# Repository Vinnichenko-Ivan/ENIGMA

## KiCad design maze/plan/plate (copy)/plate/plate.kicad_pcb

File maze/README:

//.........................................................................................//
// Этот код написан для соревнований RoboCup 2020 Командой Enigma                          //
// Состав команды: Винниченко Иван, Губин Сергей.                                          //
//.........................................................................................//
// This code is written for the RoboCup 2020 competition by the Enigma Team                // 
// Team: Ivan Vinnichenko, Sergey Gubin.                                                   //
//.........................................................................................//

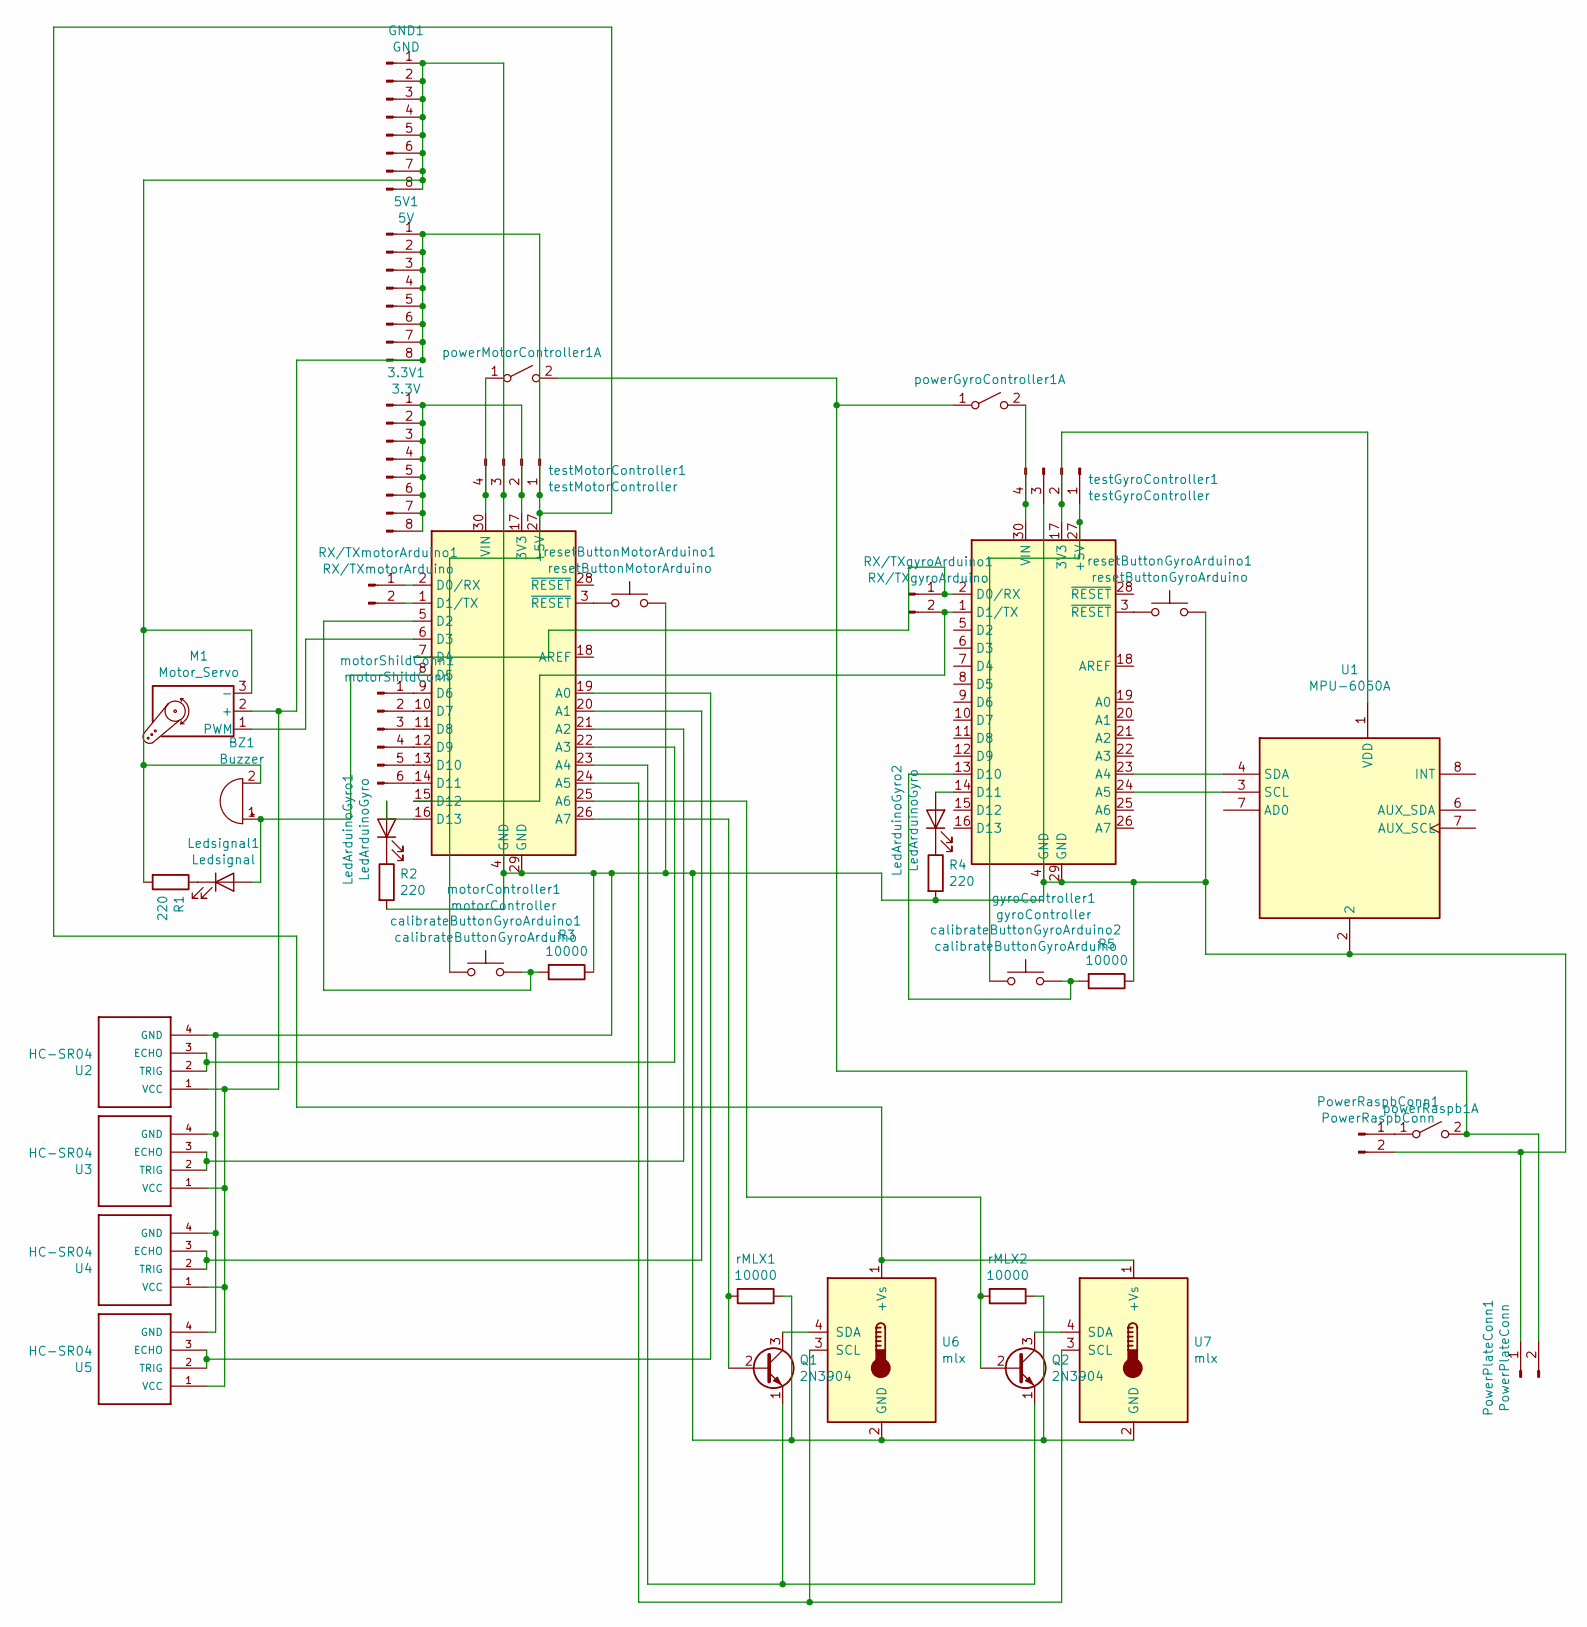
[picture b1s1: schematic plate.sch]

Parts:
3.3V1: 3.3V; PinSocket_1x08_P2.54mm_Vertical
5V1: 5V; PinSocket_1x08_P2.54mm_Vertical
BZ1: Buzzer; PinSocket_1x02_P2.54mm_Vertical
GND1: GND; PinSocket_1x08_P2.54mm_Vertical
LedArduinoGyro1, LedArduinoGyro2: LedArduinoGyro; LED_PLCC_2835
Ledsignal1: Ledsignal; PinSocket_1x02_P2.54mm_Vertical
M1: Motor_Servo; PinSocket_1x03_P2.54mm_Vertical
PowerPlateConn1: PowerPlateConn; PinHeader_1x02_P2.54mm_Vertical
PowerRaspbConn1: PowerRaspbConn; PinHeader_1x02_P2.54mm_Vertical
Q1, Q2: 2N3904; TO-92_Inline
R1, R2, R4: 220; R_1206_3216Metric
R3, R5: 10000; R_1206_3216Metric
RX/TXgyroArduino1: RX/TXgyroArduino; PinHeader_1x02_P2.54mm_Vertical
RX/TXmotorArduino1: RX/TXmotorArduino; PinHeader_1x02_P2.54mm_Vertical
U1: MPU-6050A; PinSocket_1x08_P2.54mm_Horizontal
U2, U3, U4, U5: HC-SR04; PinSocket_1x04_P2.54mm_Horizontal
U6, U7: mlx; PinHeader_1x04_P2.54mm_Vertical
calibrateButtonGyroArduino1, calibrateButtonGyroArduino2: calibrateButtonGyroArduino; SW_PUSH_6mm
gyroController1: gyroController; Arduino_Nano
motorController1: motorController; Arduino_Nano
motorShildConn1: motorShildConn; PinHeader_1x06_P2.54mm_Vertical
powerGyroController1: powerGyroController; PinSocket_1x02_P2.54mm_Vertical
powerMotorController1: powerGyroController; PinSocket_1x02_P2.54mm_Vertical
powerRaspb1: powerGyroController; PinSocket_1x02_P2.54mm_Vertical
rMLX1, rMLX2: 10000; R_1206_3216Metric
resetButtonGyroArduino1: resetButtonGyroArduino; SW_PUSH_6mm
resetButtonMotorArduino1: resetButtonMotorArduino; SW_PUSH_6mm
testGyroController1: testGyroController; PinHeader_1x04_P2.54mm_Vertical
testMotorController1: testMotorController; PinHeader_1x04_P2.54mm_Vertical

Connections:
unnamed: 3.3V1.1, 3.3V1.2, 3.3V1.3, 3.3V1.4, 3.3V1.5, 3.3V1.6, 3.3V1.7, 3.3V1.8, motorController1.17 (3V3), testMotorController1.2
unnamed: 5V1.1, 5V1.2, 5V1.3, 5V1.4, 5V1.5, 5V1.6, 5V1.7, 5V1.8, M1.2 (+), U2.1 (VCC), U3.1 (VCC), U4.1 (VCC), U5.1 (VCC), U6.1 (+Vs), U7.1 (+Vs), calibrateButtonGyroArduino1.1, motorController1.27 (+5V), testMotorController1.1
unnamed: BZ1.1 (-), Ledsignal1.2 (A), motorController1.8 (D5)
unnamed: BZ1.2 (+), GND1.1, GND1.2, GND1.3, GND1.4, GND1.5, GND1.6, GND1.7, GND1.8, M1.3 (-), PowerPlateConn1.1, PowerRaspbConn1.2, R1.2, R2.2, R3.1, R4.2, R5.1, U1.2, U2.4 (GND), U3.4 (GND), U4.4 (GND), U5.4 (GND), U6.2 (GND), U7.2 (GND), gyroController1.4 (GND), gyroController1.29 (GND), motorController1.4 (GND), motorController1.29 (GND), rMLX1.1, rMLX2.1, resetButtonGyroArduino1.2, resetButtonMotorArduino1.2, testGyroController1.3, testMotorController1.3
unnamed: LedArduinoGyro1.1 (K), R2.1
unnamed: LedArduinoGyro1.2 (A), motorController1.16 (D13)
unnamed: LedArduinoGyro2.1 (K), R4.1
unnamed: LedArduinoGyro2.2 (A), gyroController1.14 (D11)
unnamed: Ledsignal1.1 (K), R1.1
unnamed: M1.1 (PWM), motorController1.6 (D3)
unnamed: PowerPlateConn1.2, powerGyroController1.1 (A), powerMotorController1.2 (B), powerRaspb1.2 (B)
unnamed: PowerRaspbConn1.1, powerRaspb1.1 (A)
unnamed: Q1.1 (E), Q2.1 (E), motorController1.23 (A4)
unnamed: Q1.2 (B), motorController1.26 (A7), rMLX1.2
unnamed: Q1.3 (C), U6.4 (SDA)
unnamed: Q2.2 (B), motorController1.25 (A6), rMLX2.2
unnamed: Q2.3 (C), U7.4 (SDA)
unnamed: R3.2, calibrateButtonGyroArduino1.2, motorController1.5 (D2)
unnamed: R5.2, calibrateButtonGyroArduino2.2, gyroController1.13 (D10)
unnamed: RX/TXgyroArduino1.1, gyroController1.2 (D0/RX), motorController1.7 (D4)
unnamed: RX/TXgyroArduino1.2, gyroController1.1 (D1/TX), motorController1.15 (D12)
unnamed: RX/TXmotorArduino1.1, motorController1.2 (D0/RX)
unnamed: RX/TXmotorArduino1.2, motorController1.1 (D1/TX)
unnamed: U1.1 (VDD), gyroController1.17 (3V3), testGyroController1.2
unnamed: U1.3 (SCL), gyroController1.24 (A5)
unnamed: U1.4 (SDA), gyroController1.23 (A4)
unnamed: U2.2 (TRIG), U2.3 (ECHO), motorController1.22 (A3)
unnamed: U3.2 (TRIG), U3.3 (ECHO), motorController1.21 (A2)
unnamed: U4.2 (TRIG), U4.3 (ECHO), motorController1.20 (A1)
unnamed: U5.2 (TRIG), U5.3 (ECHO), motorController1.19 (A0)
unnamed: U6.3 (SCL), U7.3 (SCL), motorController1.24 (A5)
unnamed: calibrateButtonGyroArduino2.1, gyroController1.27 (+5V), testGyroController1.1
unnamed: gyroController1.3 (~RESET), resetButtonGyroArduino1.1
unnamed: gyroController1.30 (VIN), powerGyroController1.2 (B), testGyroController1.4
unnamed: motorController1.3 (~RESET), resetButtonMotorArduino1.1
unnamed: motorController1.9 (D6), motorShildConn1.1
unnamed: motorController1.10 (D7), motorShildConn1.2
unnamed: motorController1.11 (D8), motorShildConn1.3
unnamed: motorController1.12 (D9), motorShildConn1.4
unnamed: motorController1.13 (D10), motorShildConn1.5
unnamed: motorController1.14 (D11), motorShildConn1.6
unnamed: motorController1.30 (VIN), powerMotorController1.1 (A), testMotorController1.4

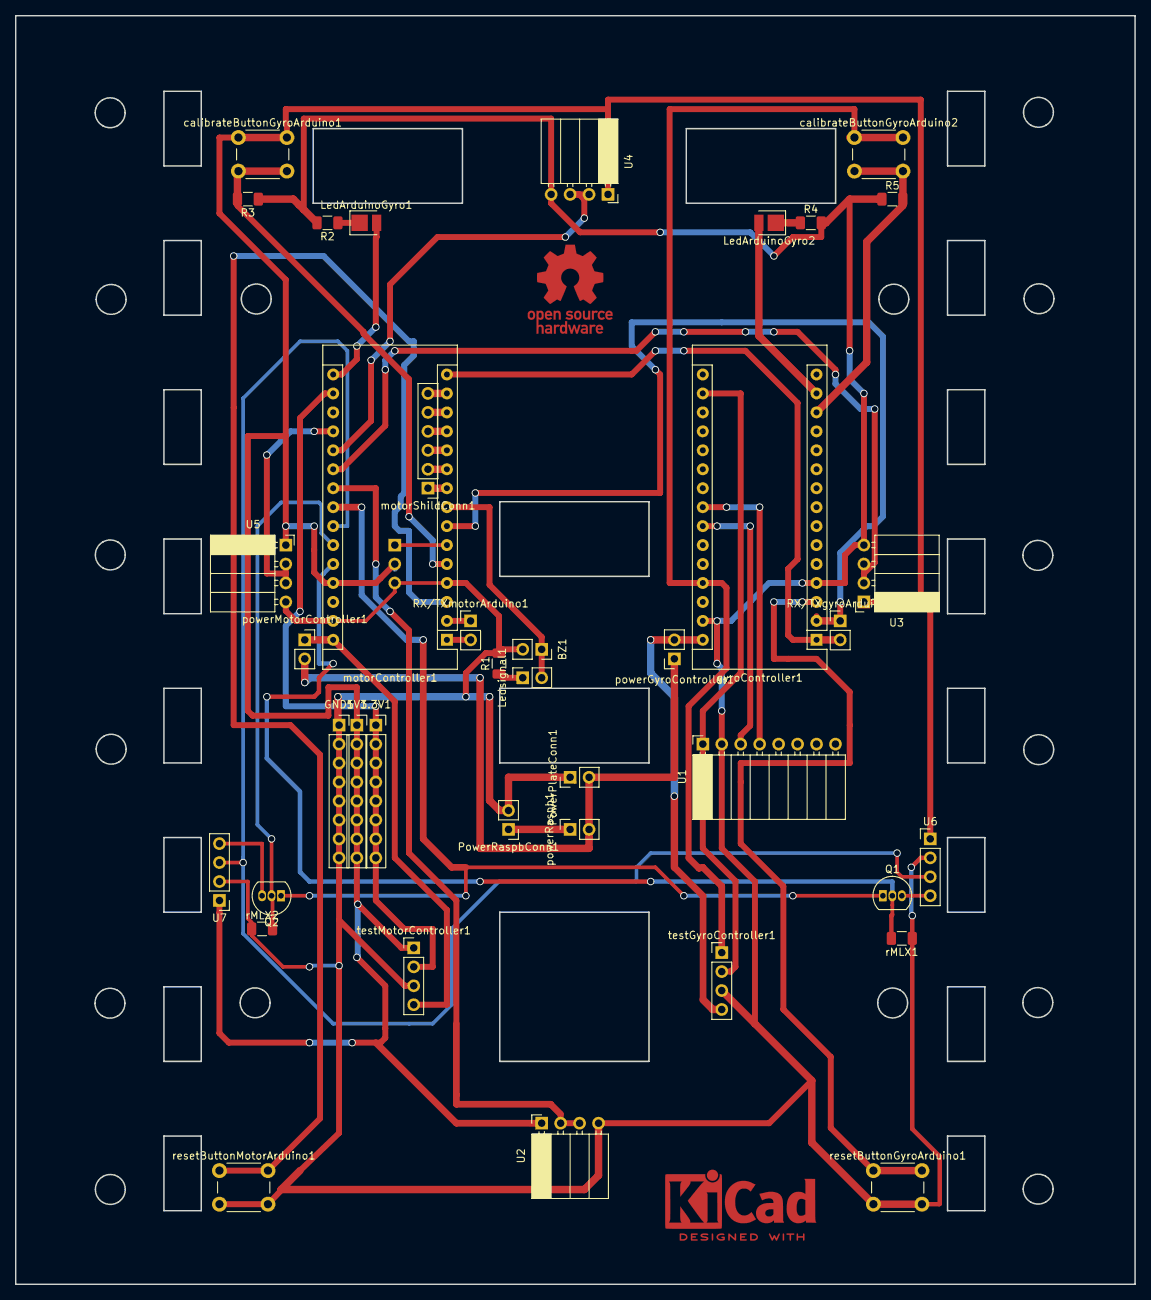
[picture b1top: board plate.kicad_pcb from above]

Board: 2 copper layers, 150.0 x 170.0 mm, 40 parts (1 on the bottom side), 42 nets.

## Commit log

2019-05-05 Old programm
    defender
2019-06-19 It is good and work program
    3 diod
2019-07-03 line
2019-09-25 Update enigma.h
    //Enigma version 1.2
    //move dont work
    //dont compile
2019-10-08 Create atacker1
2019-10-27 Update enigma.h
    gyro functional led
2019-10-27 Update enigma.h
    TABULATION
2019-10-29 Update enigma.h
    new reboot uart interface, angleGate function
2019-10-29 Update enigma.h
    repair
2019-10-29 Update atacker1
2019-10-30 Update enigma.h
    upgrade line
2019-10-31 Update enigma.h
    line upgrade
2019-11-07 Create demo
2019-11-08 Тех журнал
2019-11-08 upgrade gyro algorithm
2019-11-10 Create challenge
2019-12-02 class colorSensor
2019-12-03 Create Robocar
2019-12-03 Update Robocar
2020-01-01 Create simulathion
2020-01-01 Update simulathion
2020-03-04 Create groundControll.h
    drop box
2020-03-04 Update groundControll.h
    PID
2020-03-04 Update groundControll.h
    add
2020-03-10 Update groundControll.h
    add new interface
2020-03-10 Create newGyro
2020-03-10 Create testTurn
2020-03-27 Create opencv
2020-03-27 Update opencv
2020-04-08 Rename GyroNano to robofootball/GyroNano
2020-04-08 Rename atacker1 to robofootball/atacker1
2020-04-08 Rename challenge to robofootball/challenge
2020-04-08 Rename demo to robofootball/demo
2020-04-08 Rename enigma.h to robofootball/enigma.h
2020-04-08 Rename enigma2.h to robofootball/enigma2.h
2020-04-08 Rename tester2.8Release_notAtacher.ino to robofootball/tester2.8Release_notAtacher.ino
2020-04-08 Rename tester3.1.ino to robofootball/tester3.1.ino
2020-04-08 Rename tester3.1error.ino to robofootball/tester3.1error.ino
